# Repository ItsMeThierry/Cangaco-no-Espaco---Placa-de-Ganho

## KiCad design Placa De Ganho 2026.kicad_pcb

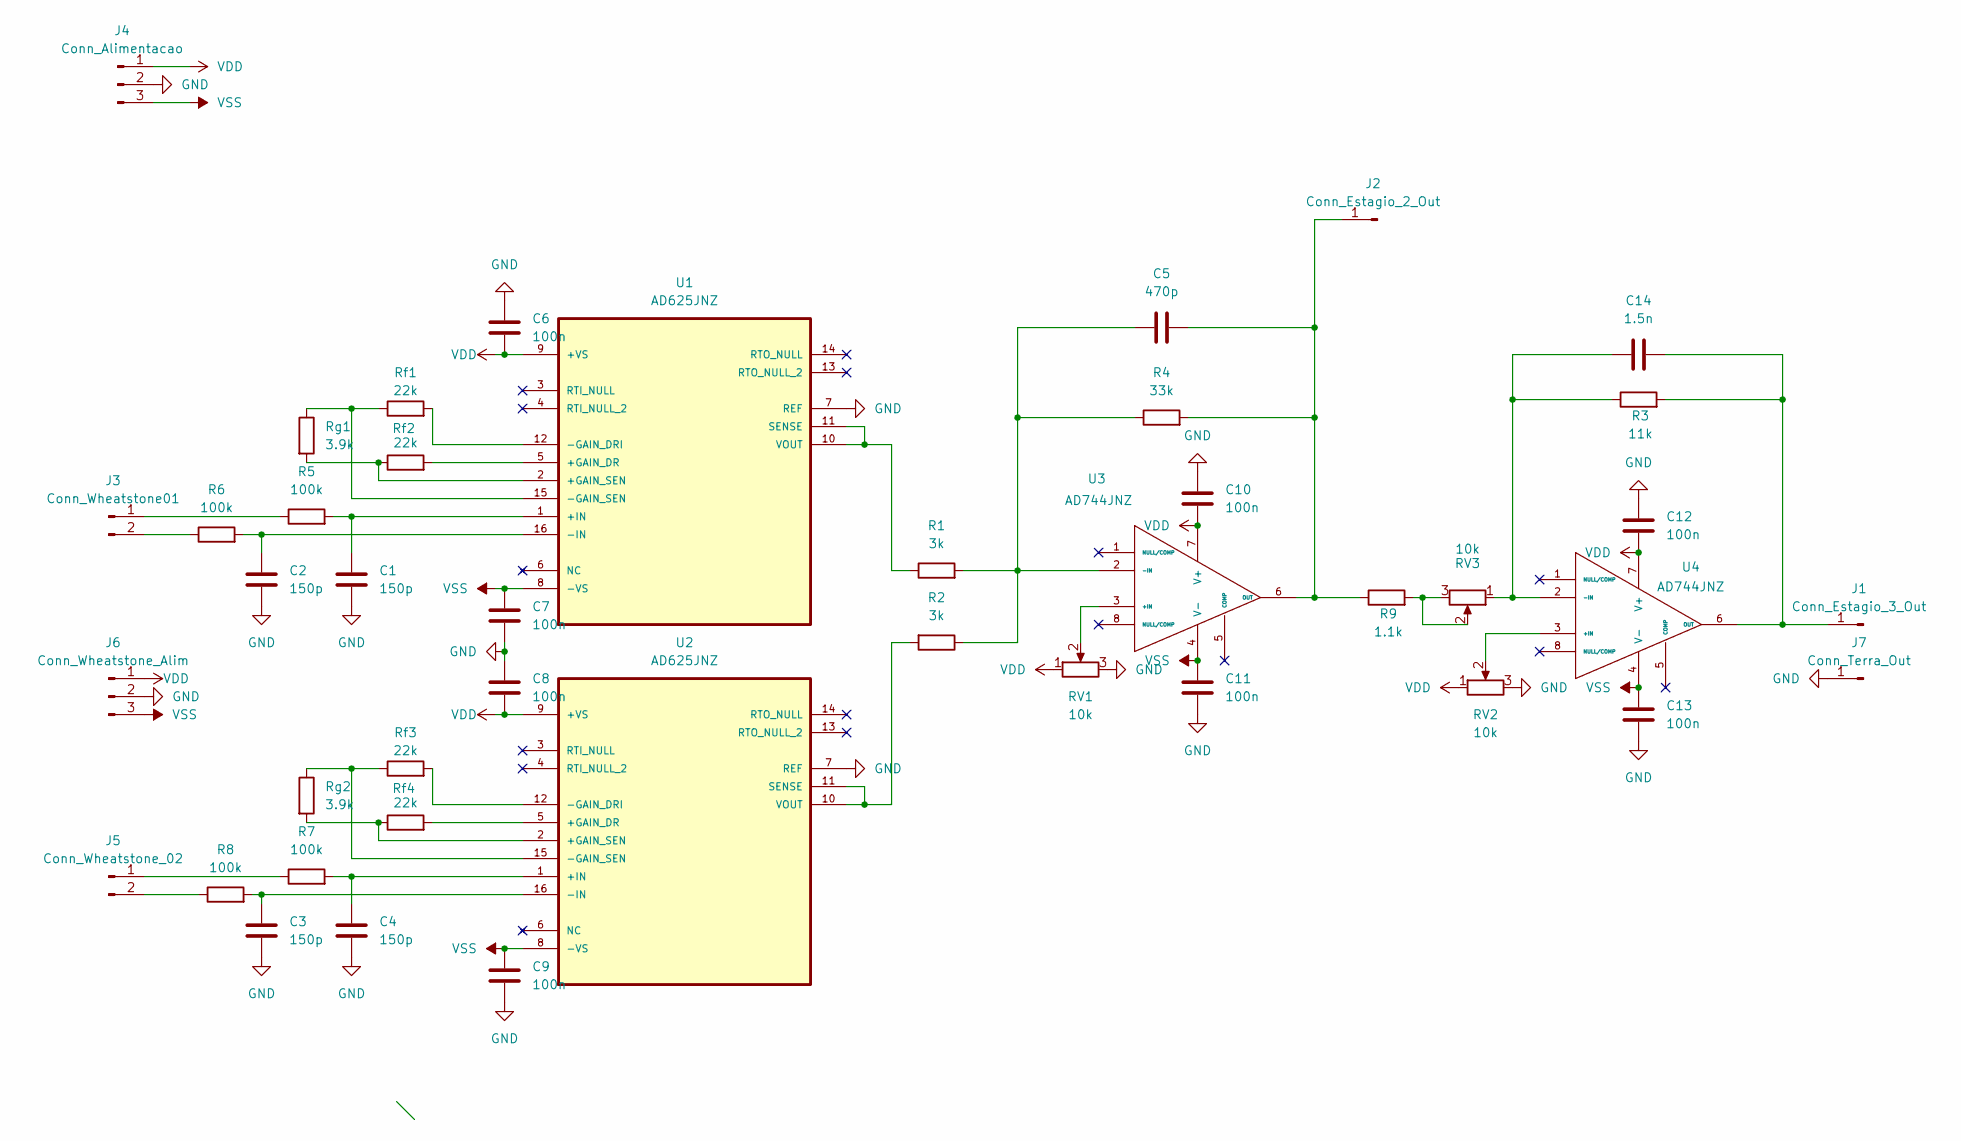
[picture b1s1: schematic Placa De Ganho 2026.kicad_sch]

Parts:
C1, C2, C3, C4: 150p; C_Disc_D3.0mm_W2.0mm_P2.50mm
C5: 470p; C_Disc_D3.0mm_W2.0mm_P2.50mm
C6, C7, C8, C9, C10, C11, C12, C13: 100n; C_Disc_D3.0mm_W2.0mm_P2.50mm
C14: 1.5n; C_Disc_D3.0mm_W2.0mm_P2.50mm
J1: Conn_Estagio_3_Out; Pin_D1.0mm_L10.0mm
J2: Conn_Estagio_2_Out; Pin_D1.0mm_L10.0mm
J3: Conn_Wheatstone01; CANGACO_PinHeader_1x02_0.8mm
J4: Conn_Alimentacao; TerminalBlock_CUI_TB007-508-03_1x03_P5.08mm_Horizontal
J5: Conn_Wheatstone_02; CANGACO_PinHeader_1x02_0.8mm
J6: Conn_Wheatstone_Alim; TerminalBlock_CUI_TB007-508-03_1x03_P5.08mm_Horizontal
J7: Conn_Terra_Out; Pin_D1.0mm_L10.0mm
R1, R2: 3k; CANGACO_Resistor_0.8mm
R3: 11k; CANGACO_Resistor_0.8mm
R4: 33k; CANGACO_Resistor_0.8mm
R5, R6, R7, R8: 100k; CANGACO_Resistor_0.8mm
R9: 1.1k; CANGACO_Resistor_0.8mm
RV1, RV2, RV3: 10k; SPACE-Potentiometer_Bourns_3296W_Vertical
Rf1, Rf2, Rf3, Rf4: 22k; CANGACO_Resistor_0.8mm
Rg1, Rg2: 3.9k; CANGACO_Resistor_0.8mm
U1, U2: AD625JNZ; DIP254P762X432-16; MPN AD625JNZ
U3, U4: AD744JNZ; DIP254P762X533-8; MPN AD744JNZ

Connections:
GND: C1.2, C2.2, C3.2, C4.2, C6.1, C7.2, C8.1, C9.2, C10.1, C11.2, C12.1, C13.2, J4.2, J6.2, J7.1, RV1.3, RV2.3, U1.7 (REF), U2.7 (REF)
unnamed: C14.1, J1.1, R3.2, U4.6 (OUT)
unnamed: C5.1, J2.1, R4.2, R9.1, U3.6 (OUT)
unnamed: J3.1, R5.1
unnamed: J3.2, R6.1
unnamed: J5.1, R7.1
unnamed: J5.2, R8.1
unnamed: R9.2, RV3.2, RV3.3
unnamed: Rf2.2, U1.5 (+GAIN_DR)
unnamed: Rf2.1, Rg1.2, U1.2 (+GAIN_SEN)
unnamed: C1.1, R5.2, U1.1 (+IN)
unnamed: Rf1.2, U1.12 (-GAIN_DRI)
unnamed: Rf1.1, Rg1.1, U1.15 (-GAIN_SEN)
unnamed: C2.1, R6.2, U1.16 (-IN)
unnamed: R1.1, U1.10 (VOUT), U1.11 (SENSE)
unnamed: Rf4.2, U2.5 (+GAIN_DR)
unnamed: Rf4.1, Rg2.2, U2.2 (+GAIN_SEN)
unnamed: C4.1, R7.2, U2.1 (+IN)
unnamed: Rf3.2, U2.12 (-GAIN_DRI)
unnamed: Rf3.1, Rg2.1, U2.15 (-GAIN_SEN)
unnamed: C3.1, R8.2, U2.16 (-IN)
unnamed: R2.2, U2.10 (VOUT), U2.11 (SENSE)
unnamed: RV1.2, U3.3 (+IN)
unnamed: C5.2, R1.2, R2.1, R4.1, U3.2 (-IN)
unnamed: RV2.2, U4.3 (+IN)
unnamed: C14.2, R3.1, RV3.1, U4.2 (-IN)
VDD: C6.2, C8.2, C10.2, C12.2, J4.1, J6.1, RV1.1, RV2.1, U1.9 (+VS), U2.9 (+VS), U3.7 (V+), U4.7 (V+)
VSS: C7.1, C9.1, C11.1, C13.1, J4.3, J6.3, U1.8 (-VS), U2.8 (-VS), U3.4 (V-), U4.4 (V-)

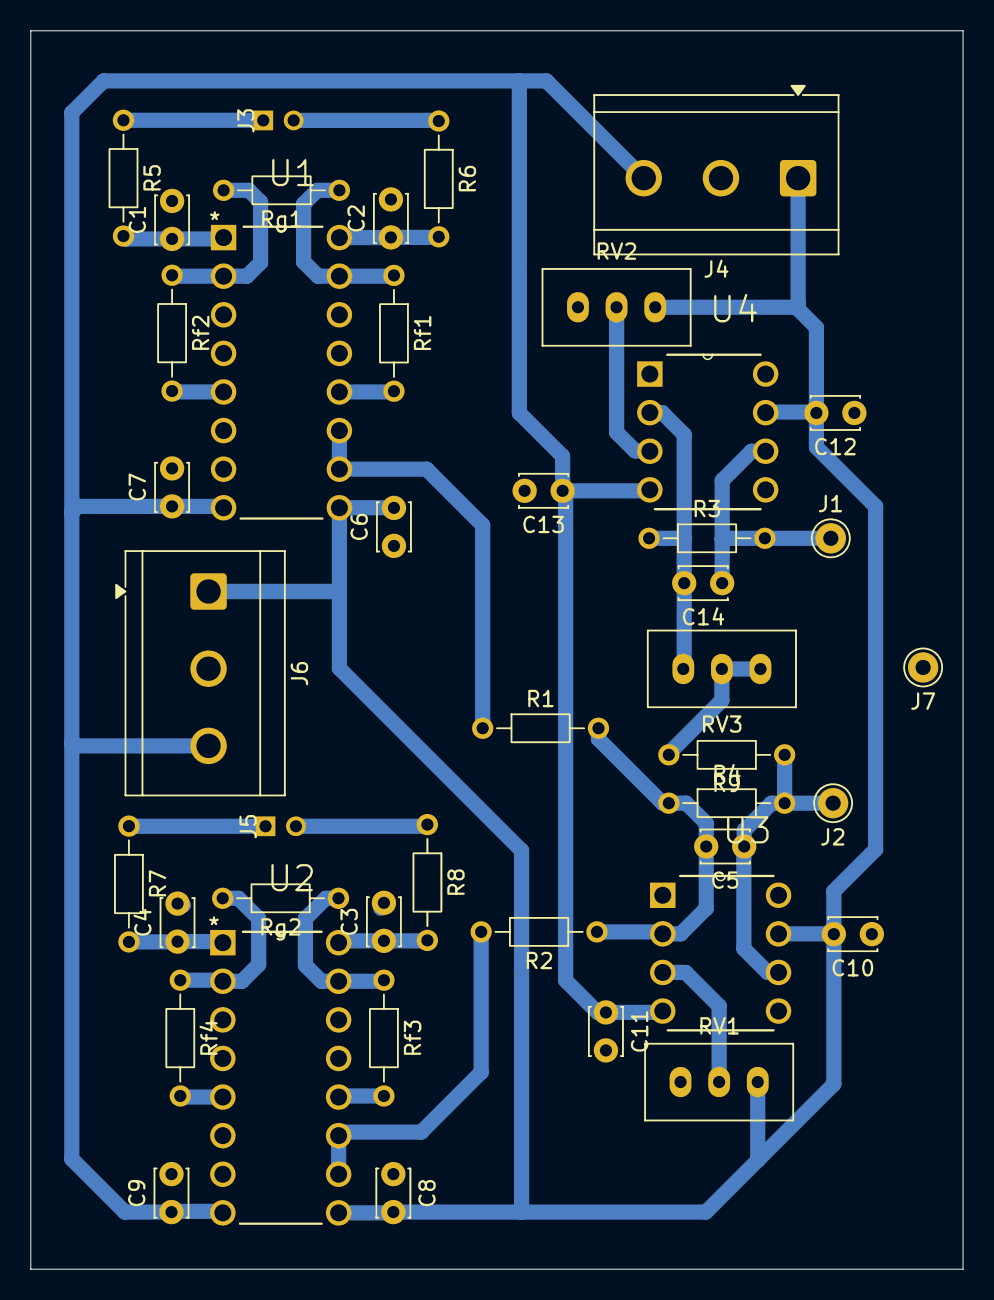
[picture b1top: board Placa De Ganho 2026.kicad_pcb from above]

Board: 2 copper layers, 61.4 x 81.5 mm, 43 parts (0 on the bottom side), 28 nets.
